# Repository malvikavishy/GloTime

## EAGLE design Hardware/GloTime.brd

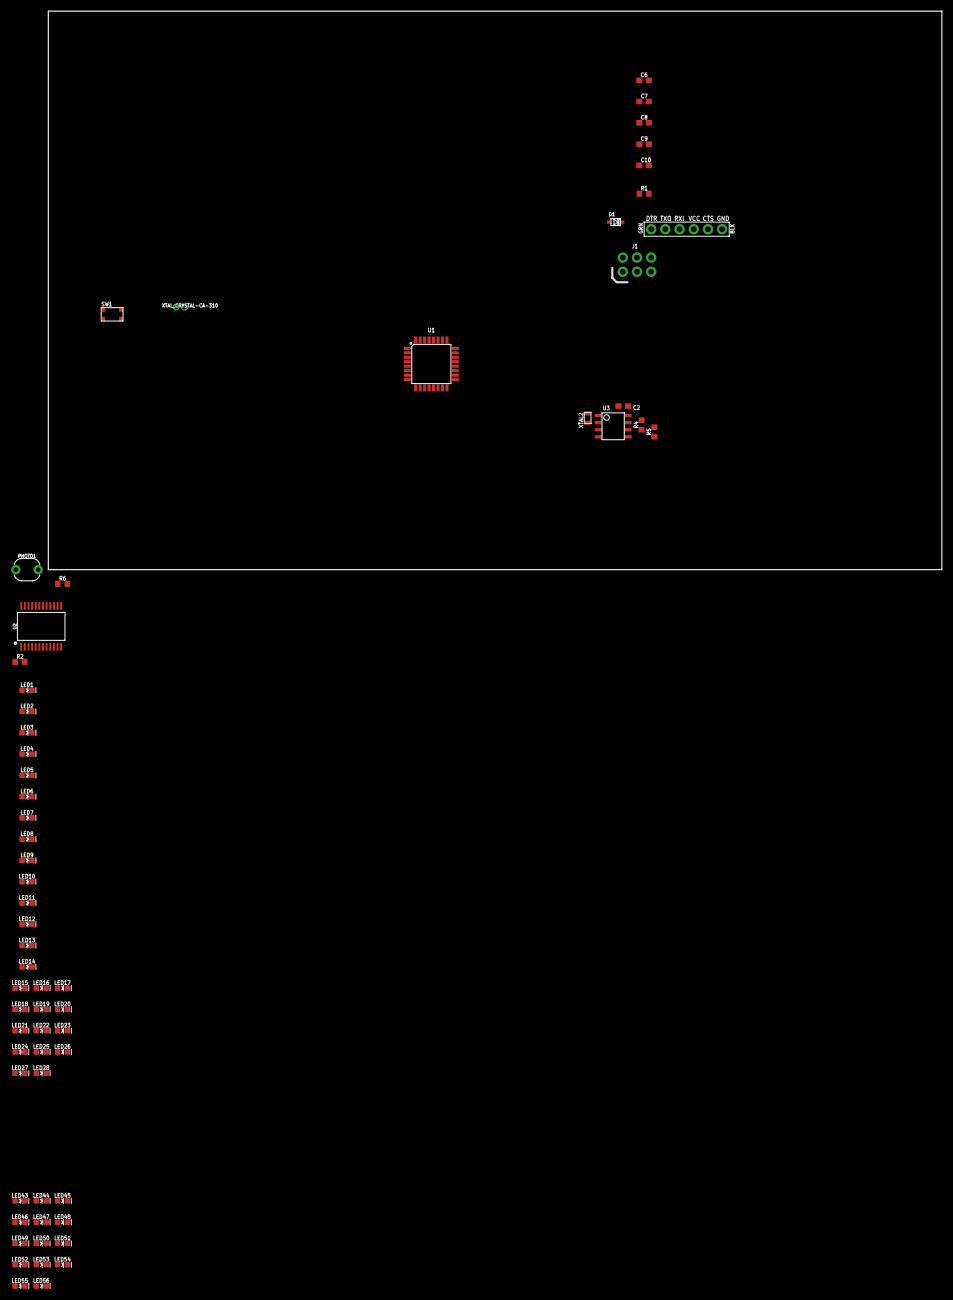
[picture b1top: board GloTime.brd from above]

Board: 2 copper layers, 160.0 x 100.0 mm, 63 parts (0 on the bottom side), 45 nets, no tracks yet.

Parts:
C2: 1u; C0603
C6, C7: 0.1u; C0603
C8: 2.2u; C0603
C9, C10: 22p; C0603
D1: USC
FTDI1: FTDI_DEVICE
J1: AVR_SPI_PROG_3X2NS; 2X3-NS
LED1, LED2, LED3, LED4, LED5, LED6, LED7, LED8, LED9, LED10, LED11, LED12, LED13, LED14, LED15, LED16, LED17, LED18, LED19, LED20, LED21, LED22, LED23, LED24, LED25, LED26, LED27, LED28, LED43, LED44, LED45, LED46, LED47, LED48, LED49, LED50, LED51, LED52, LED53, LED54, LED55, LED56: LED-0603
PHOTO1: PHOTOCELLPTH; PHOTOCELL
R1, R2, R4, R5, R6: 10k; R0603
SW1: BUTTON-GULLWING
U1: ATMEGA328P_TQFP; TQFP32-08
U2: CD74HC4067SM96; SSOP24
U3: PCF8523; SO8
XTAL2: 32.7680kHz; 2-SMD.NOLEAD.2.0MMTO1.2MM
XTAL_CRYSTAL-CA-310: CA-301

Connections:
3.3V: C2.1, R4.2, R5.2, U3.8
A10/CHAN8: LED1.A, LED2.A, U2.23
B10/CHAN9: LED3.A, LED4.A, U2.22
C10/CHAN10: LED5.A, LED6.A, U2.21
D10/CHAN11: LED7.A, LED8.A, U2.20
DTR: C6.1, FTDI1.DTR
E10/CHAN12: LED9.A, LED10.A, U2.19
F10/CHAN13: LED11.A, LED11.C, LED12.A, U2.18
G10/CHAN14: LED13.A, LED14.A, U2.17
GND: C2.2, C7.2, C8.2, C9.2, C10.2, FTDI1.CTS, FTDI1.GND, J1.6, PHOTO1.1, SW1.3, SW1.4, U1.3, U1.5, U1.21, U3.4
LD1/S2: U1.2, U2.14
LD2/S1: U1.1, U2.11
LD3/S0: U1.32, U2.10
LD9: J1.3, U1.17
LD10: J1.1, U1.16
LD11: J1.4, U1.15
LD16/E: PHOTO1.2, R6.1, U1.10, U2.15
MODE/S3: U1.9, U2.13
unnamed: C10.1, U1.7, XTAL_CRYSTAL-CA-310.2
unnamed: C9.1, U1.8, XTAL_CRYSTAL-CA-310.1
unnamed: U3.2, XTAL2.P$1
unnamed: U3.1, XTAL2.P$2
unnamed: C7.1, C8.1
unnamed: D1.+, FTDI1.VCC
unnamed: R2.1, U2.1
unnamed: LED25.A, LED25.C, LED26.A
unnamed: LED15.A, LED16.A
unnamed: LED17.A, LED18.A
unnamed: LED19.A, LED20.A
unnamed: LED27.A, LED28.A
unnamed: LED23.A, LED24.A
unnamed: LED21.A, LED22.A
unnamed: LED53.A, LED53.C, LED54.A
unnamed: LED43.A, LED44.A
unnamed: LED45.A, LED46.A
unnamed: LED47.A, LED48.A
unnamed: LED55.A, LED56.A
unnamed: LED51.A, LED52.A
unnamed: LED49.A, LED50.A
RESET: C6.2, J1.5, R1.1, SW1.1, SW1.2, U1.29
RXD: FTDI1.TXO, U1.30
SCL: R4.1, U3.6
SDA: R5.1, U3.5
TXD: FTDI1.RXI, U1.31
VCC: D1.-, J1.2, R1.2, R2.2, U1.4, U1.6, U1.18

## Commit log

2021-02-20 Mood Mark Description
2021-02-20 Mood Marker Board
2021-02-20 Mood Marker Schematic
2021-02-20 Mood Marker BOM
2021-02-20 GloTime Board
2021-02-20 GloTime Schematic
2021-02-20 GloTime BOM
2021-02-20 GloTime Description
2021-02-20 GloTime Diagram
2021-03-06 Updated Board
2021-03-06 Updated Schematic

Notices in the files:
parts and their libraries:
SparkFun-IC-Logic: Licensing: Creative Commons ShareAlike 4.0 International - https://creativecommons.org/licenses/by-sa/4.0
